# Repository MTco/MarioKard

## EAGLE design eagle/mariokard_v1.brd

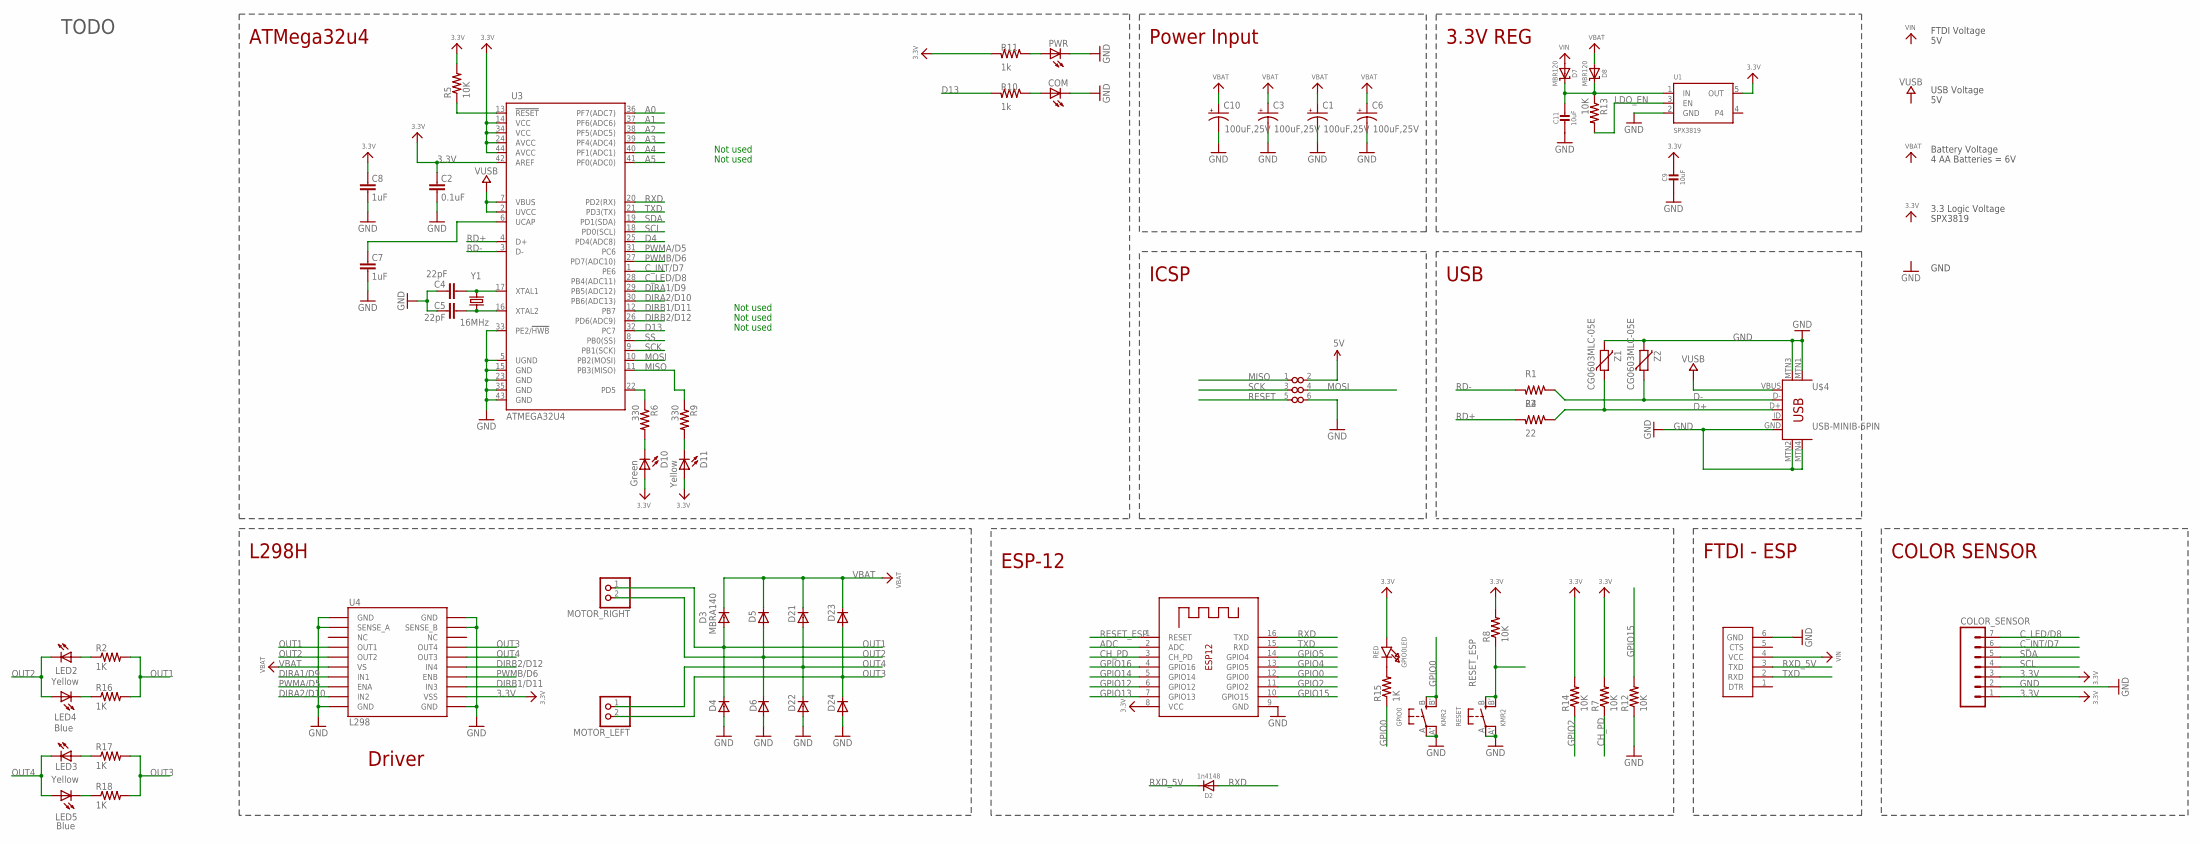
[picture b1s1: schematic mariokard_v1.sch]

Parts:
C1, C3, C6, C10: 100uF,25V; NIPPON_F80
C2: 0.1uF; 0603-CAP
C4, C5: 22pF; 0603-CAP
C7, C8: 1uF; 0603-CAP
C9, C11: 10uF; 0805-NO
COLOR_SENSOR: M07; 1X07
COM: LEDCHIPLED_0603; CHIPLED_0603
D2: 1n4148; SOD-323
D3, D4, D5, D6, D21, D22, D23, D24: MBRA140; SMA-DIODE
D7, D8: MBR120; SOD-123
D10: Green; LED-0603
D11: Yellow; LED-0603
FTDI: FTDI_POGO
GPIO0: KMR2; BTN_KMR2_4.6X2.8
GPIO0LED: RED; CHIPLED_0805_NOOUTLINE
ISP: ISP_POGO; POGO_ISP
LED2, LED3: Yellow; LED-0603
LED4, LED5: Blue; LED-0603
MOTOR_LEFT: JST_2PIN-SMT-RA; JST-PH-2-SMT-RA
MOTOR_RIGHT: JST_2PIN-SMT-RA; JST-PH-2-SMT-RA
PWR: LEDCHIPLED_0603; CHIPLED_0603
R1, R4: 22; 0805
R2, R16, R17, R18: 1K; 0402-RES
R5: 10K; 0603-RES
R6, R9: 330; 0603-RES
R7, R8, R12, R13, R14: 10K; R0603
R10, R11: 1k; 0805
R15: 1K; R0603
RESET: KMR2; BTN_KMR2_4.6X2.8
U1: SPX3819; SOT23-5
U3: ATMEGA32U4; TQFP44
U4: L298; POWERSO20
U$4: USB-MINIB-5PIN; USB-MINIB
X1: ESP-12
Y1: 16MHz; CRYSTAL-SMD-5X3
Z1, Z2: CG0603MLC-05E; CT/CN0603

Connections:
3.3V: C2.2, C8.2, C9.1, COLOR_SENSOR.1, COLOR_SENSOR.3, D10.A, D11.A, GPIO0LED.A, R5.2, R7.2, R8.2, R11.2, R14.2, U1.5 (OUT), U3.14 (VCC), U3.24 (AVCC), U3.34 (VCC), U3.42 (AREF), U3.44 (AVCC), U4.P$12 (VSS), X1.8 (VCC)
A0: U3.36 (PF7(ADC7))
A1: U3.37 (PF6(ADC6))
A2: U3.38 (PF5(ADC5))
A3: U3.39 (PF4(ADC4))
A4: U3.40 (PF1(ADC1))
A5: U3.41 (PF0(ADC0))
ADC: X1.2 (ADC)
CH_PD: R7.1, X1.3 (CH_PD)
C_INT/D7: COLOR_SENSOR.6, U3.1 (PE6)
C_LED/D8: COLOR_SENSOR.7, U3.28 (PB4(ADC11))
D4: U3.25 (PD4(ADC8))
D13: R10.2, U3.32 (PC7)
D+: R4.1, U$4.D+, Z1.1
D-: R1.1, U$4.D-, Z2.1
DIRA1/D9: U3.29 (PB5(ADC12)), U4.P$7 (IN1)
DIRA2/D10: U3.30 (PB6(ADC13)), U4.P$9 (IN2)
DIRB1/D11: U3.12 (PB7), U4.P$13 (IN3)
DIRB2/D12: U3.26 (PD6(ADC9)), U4.P$15 (IN4)
GND: C1.-, C2.1, C3.-, C4.2, C5.2, C6.-, C7.1, C8.1, C9.2, C10.-, C11.2, COLOR_SENSOR.2, COM.C, D4.A, D6.A, D22.A, D24.A, FTDI.6 (GND), GPIO0.A, GPIO0.A' (P1), R12.1, RESET.A, RESET.A' (P1), U1.2 (GND), U3.5 (UGND), U3.15 (GND), U3.23 (GND), U3.33 (PE2/!HWB), U3.35 (GND), U3.43 (GND), U4.P$1 (GND), U4.P$2 (SENSE_A), U4.P$10 (GND), U4.P$11 (GND), U4.P$19 (SENSE_B), U4.P$20 (GND), U$4.GND, U$4.MTN1 (MTN2), U$4.MTN2 (MTN3), U$4.MTN3 (MTN1), U$4.MTN4, X1.9 (GND), Z1.2, Z2.2
GPIO0: GPIO0.B (S), GPIO0.B' (S1), R15.1, X1.12 (GPIO0)
GPIO2: R14.1, X1.11 (GPIO2)
GPIO4: X1.13 (GPIO5)
GPIO5: X1.14 (GPIO4)
GPIO12: X1.6 (GPIO12)
GPIO13: X1.7 (GPIO13)
GPIO14: X1.5 (GPIO14)
GPIO15: R12.2, X1.10 (GPIO15)
GPIO16: X1.4 (GPIO16)
LDO_EN: R13.2, U1.3 (EN)
MISO: ISP.1 (MISO), R9.1, U3.11 (PB3(MISO))
MOSI: ISP.4 (MOSI), U3.10 (PB2(MOSI))
unnamed: C5.1, U3.16 (XTAL2), Y1.1
unnamed: C4.1, U3.17 (XTAL1), Y1.3 (2)
unnamed: C7.2, U3.6 (UCAP)
unnamed: C11.1, D7.C, D8.C, R13.1, U1.1 (IN)
unnamed: LED2.A, R2.1
unnamed: LED4.C, R16.1
unnamed: LED5.C, R18.1
unnamed: LED3.A, R17.1
unnamed: COM.A, R10.1
unnamed: PWR.A, R11.1
unnamed: GPIO0LED.C, R15.2
unnamed: D11.C, R9.2
unnamed: D10.C, R6.2
OUT1: D3.A, D4.C, MOTOR_RIGHT.1 (2), R2.2, R16.2, U4.P$4 (OUT1)
OUT2: D5.A, D6.C, LED2.C, LED4.A, MOTOR_RIGHT.2 (1), U4.P$5 (OUT2)
OUT3: D23.A, D24.C, MOTOR_LEFT.2 (1), R17.2, R18.2, U4.P$17 (OUT4)
OUT4: D21.A, D22.C, LED3.C, LED5.A, MOTOR_LEFT.1 (2), U4.P$16 (OUT3)
PWMA/D5: U3.31 (PC6), U4.P$8 (ENA)
PWMB/D6: U3.27 (PD7(ADC10)), U4.P$14 (ENB)
RD+: R4.2, U3.4 (D+)
RD-: R1.2, U3.3 (D-)
RESET: ISP.5 (RESET), R5.1, U3.13 (!RESET)
RESET_ESP: R8.1, RESET.B (S), RESET.B' (S1), X1.1 (RESET)
RXD: D2.A, U3.20 (PD2(RX)), X1.16 (TXD)
RXD_5V: D2.C, FTDI.3 (TXD)
SCK: ISP.3 (SCK), U3.9 (PB1(SCK))
SCL: COLOR_SENSOR.4, U3.18 (PD0(SCL))
SDA: COLOR_SENSOR.5, U3.19 (PD1(SDA))
SS: U3.8 (PB0(SS))
TXD: FTDI.2 (RXD), U3.21 (PD3(TX)), X1.15 (RXD)
TXLED1: R6.1, U3.22 (PD5)
VBAT: C1.+, C3.+, C6.+, C10.+, D3.C, D5.C, D8.A, D21.C, D23.C, U4.P$6 (VS)
VIN: D7.A, FTDI.4 (VCC)
VUSB: U3.2 (UVCC), U3.7 (VBUS), U$4.VBUS

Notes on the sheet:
3.3V REG
USB
ICSP
ATMega32u4
ESP-12
FTDI - ESP
L298H
Not used
Power Input
TODO
FTDI Voltage
USB Voltage
Battery Voltage
3.3 Logic Voltage
GND
4 AA Batteries = 6V
SPX3819
Driver
COLOR SENSOR

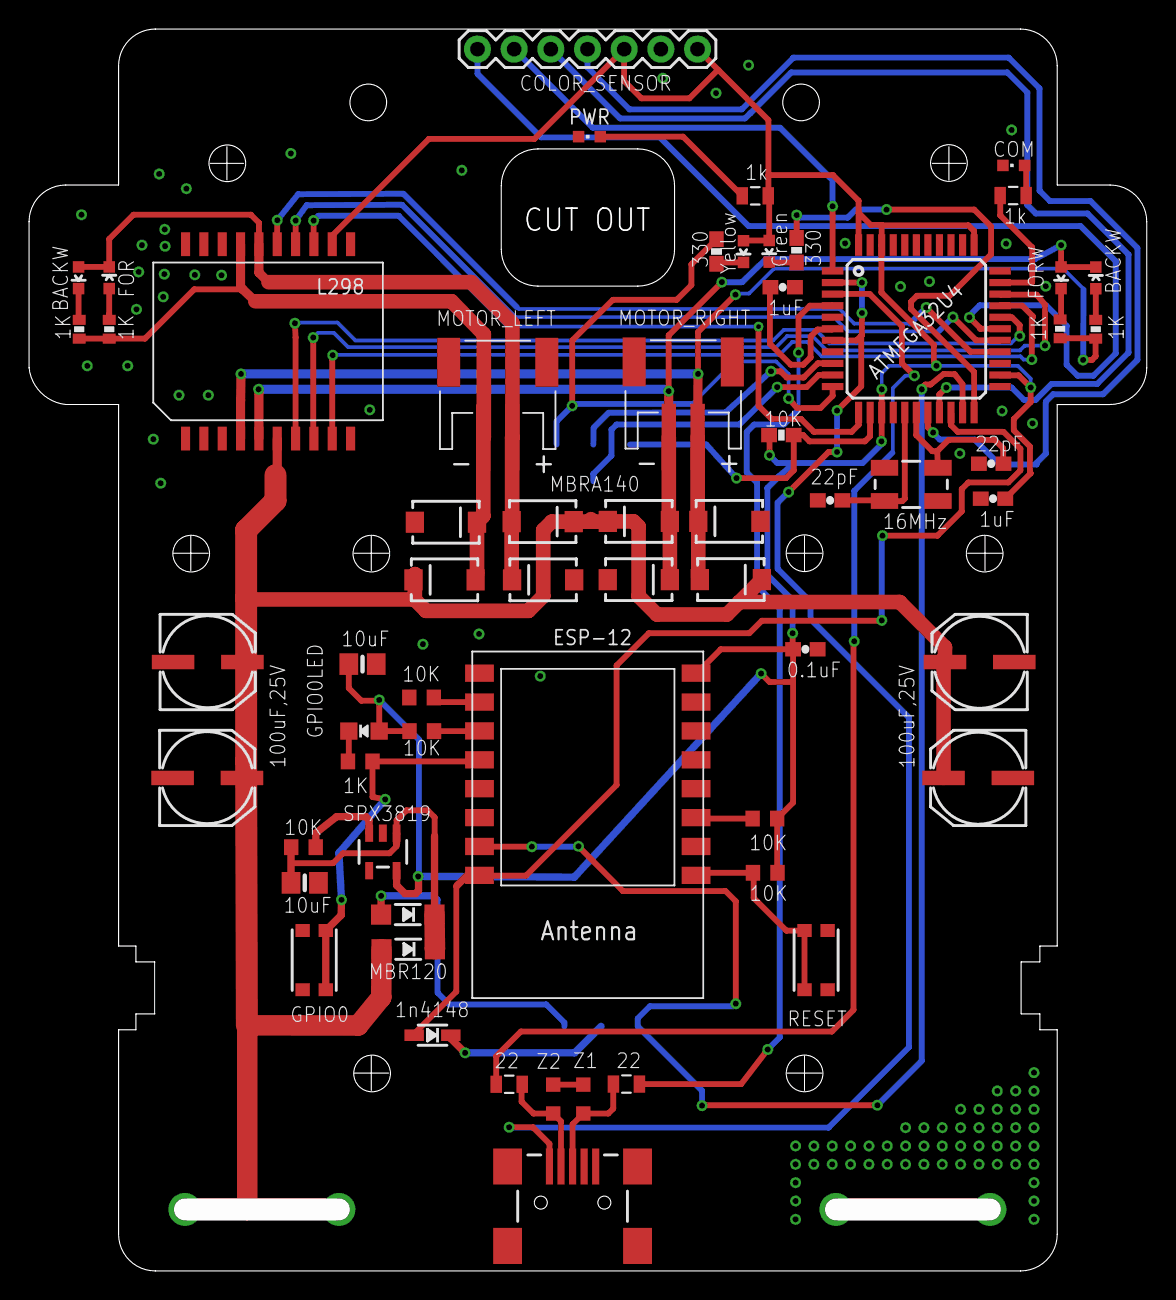
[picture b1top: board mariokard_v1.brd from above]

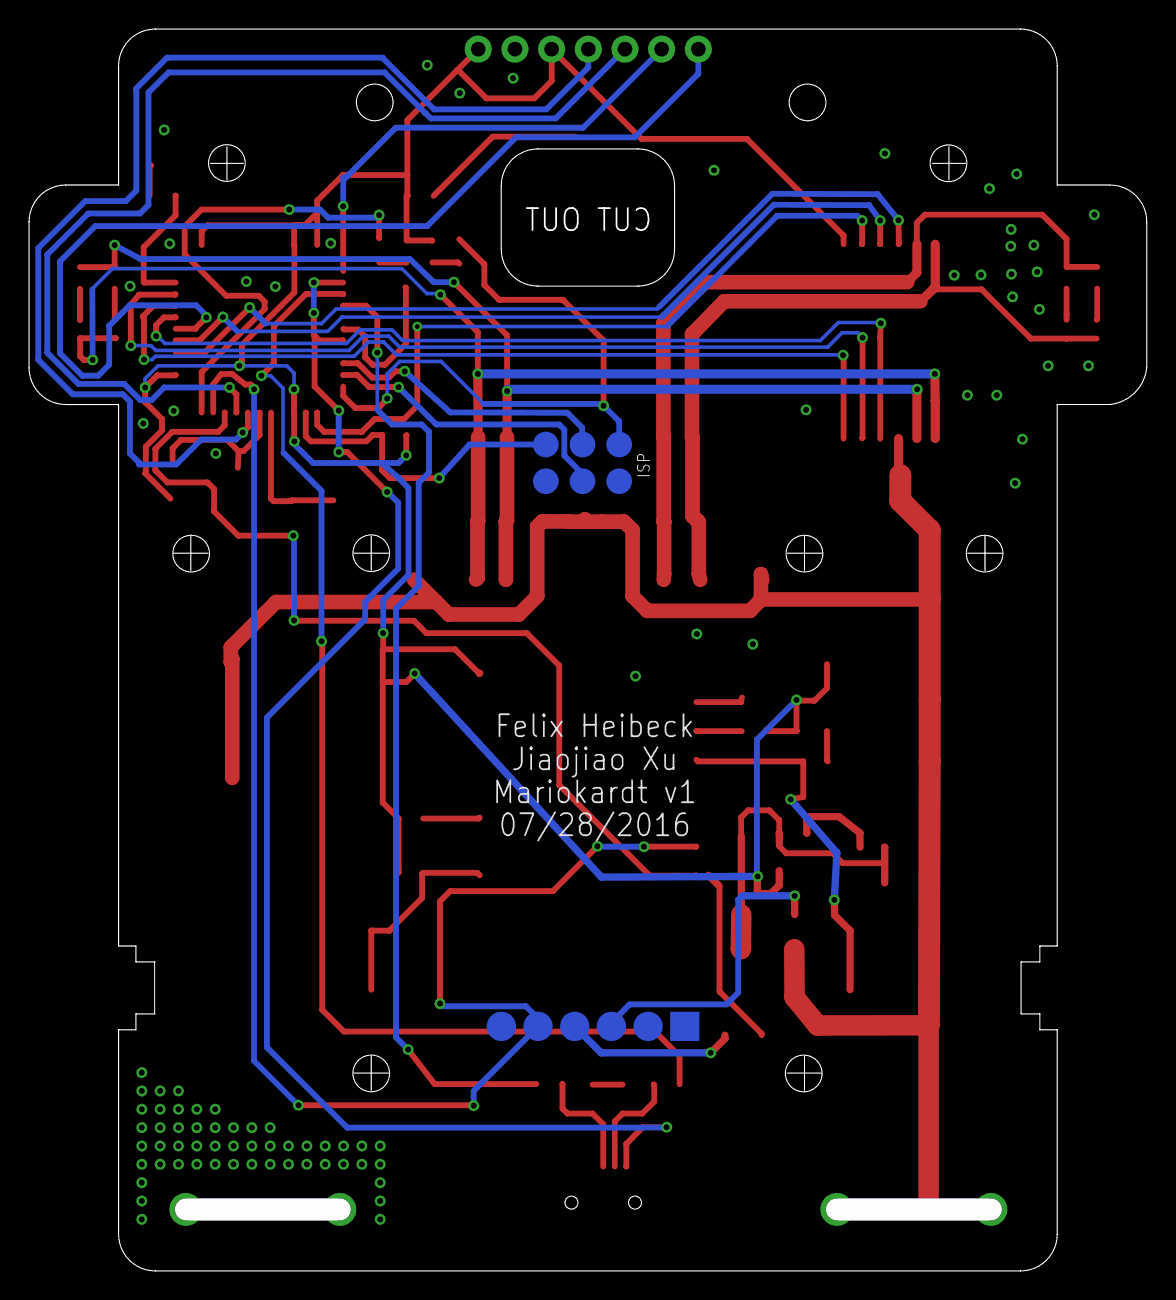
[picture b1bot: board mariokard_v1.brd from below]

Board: 2 copper layers, 77.4 x 86.0 mm, 63 parts (2 on the bottom side), 51 nets.

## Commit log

2016-07-22 WIP board init
    very much work in progress. schematic mostly done, board still in rough
    layout phase.
2016-07-25 small fixes - still WIP
2016-07-25 fixed copy-paste error
2016-07-28 v1 - still needs to be tested
2016-10-07 new board iteration. also pull from master.

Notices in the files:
parts and their libraries:
SparkFun-Connectors: Licensing: Creative Commons ShareAlike 4.0 International - https://creativecommons.org/licenses/by-sa/4.0
microbuilder: This work is placed in the public domain, and may be freely used for commercial and non-commercial work with the following conditions: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
